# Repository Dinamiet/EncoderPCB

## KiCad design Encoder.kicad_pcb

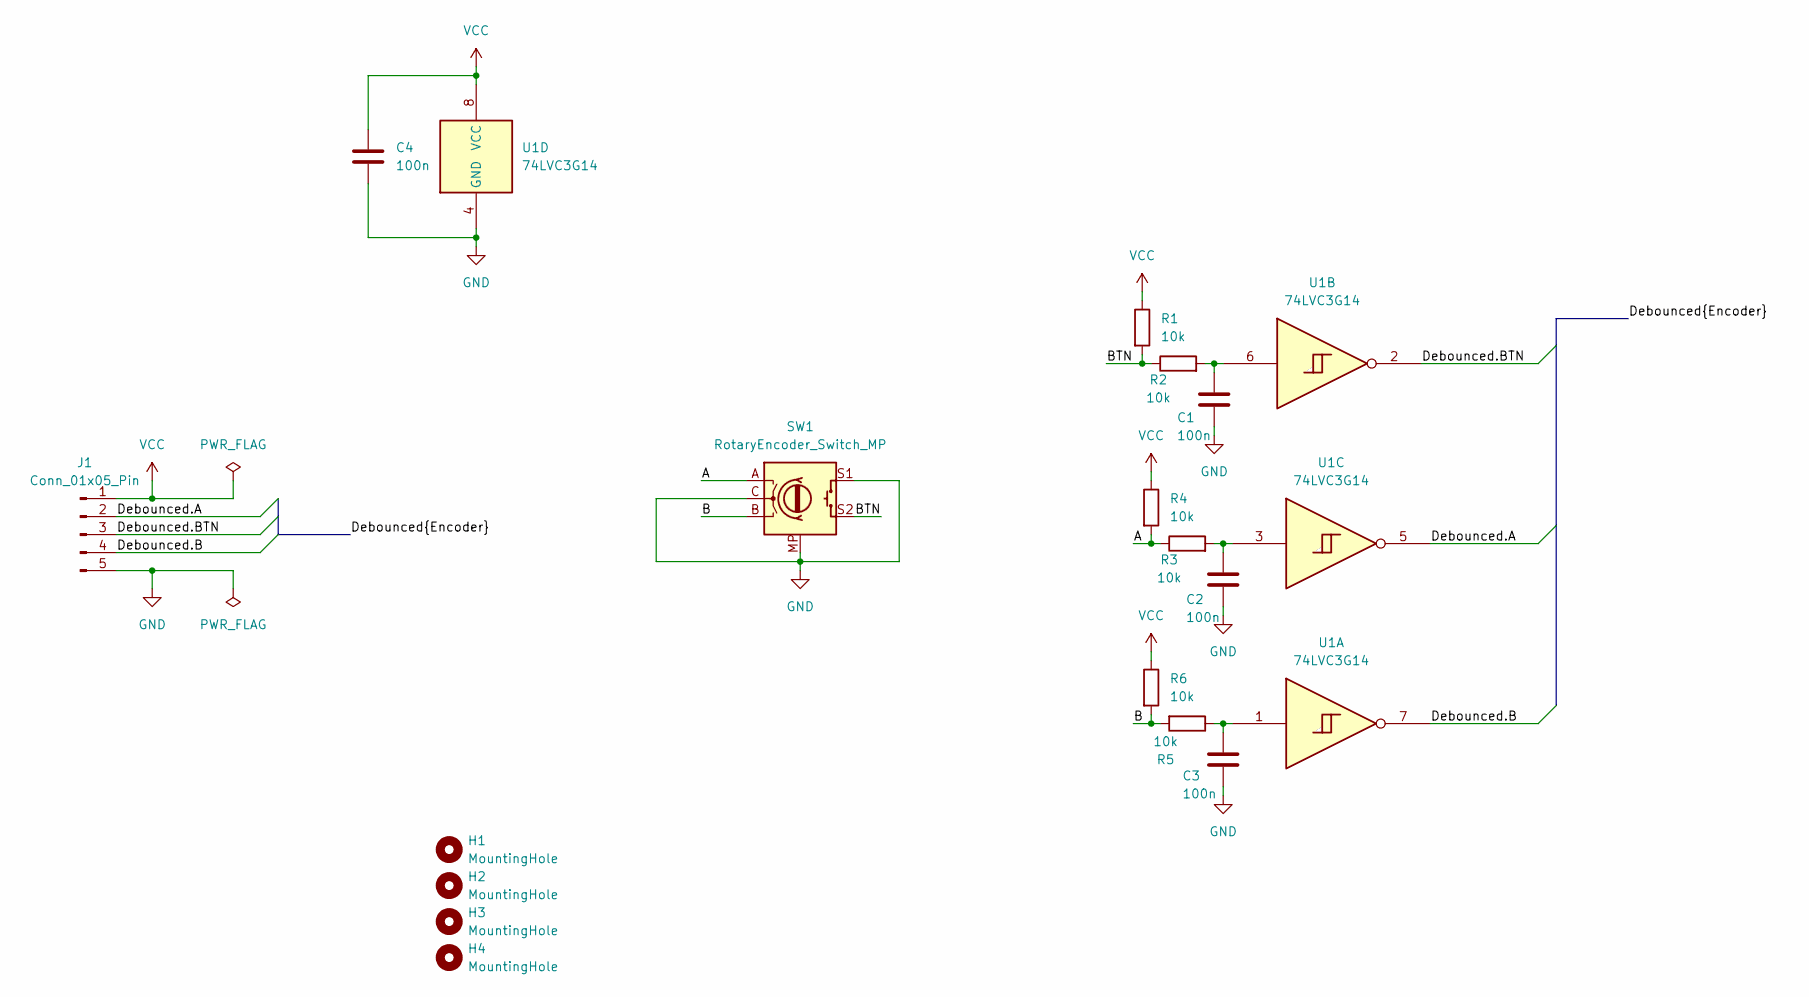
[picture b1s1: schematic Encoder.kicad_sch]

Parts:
C1, C2, C3, C4: 100n; C_1206_3216Metric_Pad1.33x1.80mm_HandSolder
H1, H2, H3, H4: MountingHole; MountingHole_2mm
J1: Conn_01x05_Pin; PinHeader_1x05_P2.54mm_Vertical
R1, R2, R3, R4, R5, R6: 10k; R_1206_3216Metric_Pad1.30x1.75mm_HandSolder
SW1: RotaryEncoder_Switch_MP; RotaryEncoder_Alps_EC12E-Switch_Vertical_H20mm; LCSC C470596
U1: 74LVC3G14; VSSOP-8_2.3x2mm_P0.5mm; LCSC C98856

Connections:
/A: R3.1, R4.2, SW1.A
/B: R5.2, R6.2, SW1.B
/BTN: R1.2, R2.1, SW1.S2
/Debounced.A: J1.2, U1.5
/Debounced.B: J1.4, U1.7
/Debounced.BTN: J1.3, U1.2
GND: C1.2, C2.2, C3.2, C4.2, J1.5, SW1.C, SW1.MP, SW1.S1, U1.4 (GND)
unnamed: C1.1, R2.2, U1.6
unnamed: C2.1, R3.2, U1.3
unnamed: C3.1, R5.1, U1.1
VCC: C4.1, J1.1, R1.1, R4.1, R6.1, U1.8 (VCC)

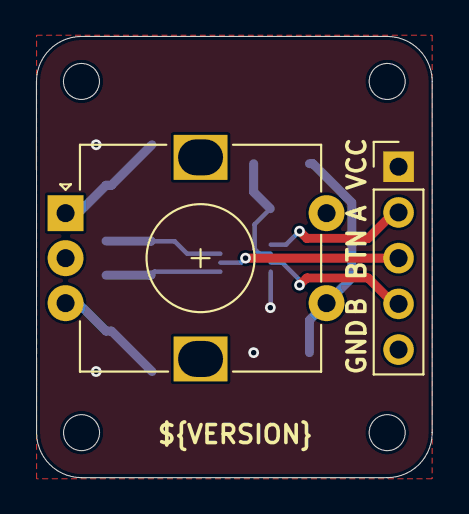
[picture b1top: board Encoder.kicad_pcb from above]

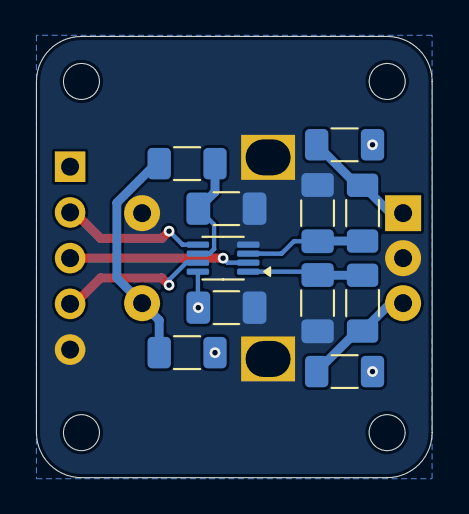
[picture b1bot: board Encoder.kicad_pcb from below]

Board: 2 copper layers, 22.0 x 24.5 mm, 17 parts (11 on the bottom side), 11 nets.

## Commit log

2025-04-19 Initial schematic
2025-04-19 Initial layout
2025-04-19 Move component references to silkscreen layer
2025-04-20 Add mounting holes
2025-04-22 Add decoupling capacitor
2025-04-22 Add funding configuration for GitHub
2025-04-26 Fix debounce routing
2025-04-26 Item movement for easier viewing
2025-06-05 Layout done
2025-06-05 Add header labels
2025-06-05 Address warnings
2025-07-04 Rounded PCB corners
2025-07-04 Add version to silkscreen
2025-07-04 Update Plot settings
2025-07-05 Update BOM options for export
